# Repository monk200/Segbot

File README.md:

# Segbot

This repository contains files such as code, CAD files, Matlab simulations, and brainstorming documents from my work designing and developing a two-wheeled balancing robot. The project can be split into two main parts: designing the system and developing the real-world version of the system. The original design was done in my [Mechatronics](http://coecsl.ece.illinois.edu/ge423/) course as a final project for Spring 2020 but the real robot was built and programmed in the course [Computer Control of Mechanical Systems](http://coecsl.ece.illinois.edu/me461/) in Fall 2020. Both courses were led by UIUC Prof. Dan Block, the university's Control Systems Lab Manager. Prof. Block created a guide to building a Segbot at [this link](http://coecsl.ece.illinois.edu/segbot/segbot.html) and his guidance and expertise was absolutely essential in all steps of this project.  

## Designing the System
Because of the COVID-19 pandemic, Prof. Block restructured the final project of Mechatronics to be to design a Segbot from scratch. At the time, the [Mechatronics course used the MPS430G2553 microcontroller](https://github.com/monk200/Mechatronics_with_MSP430G2553) so all of the initial design choices and considerations were made keeping that in mind. I compiled a list of parts that were essential for desiging a PCB that would interface with the microcontroller. I was also tasked with creating a CAD model of the robot body and using its parameters, as well as the parameters of the motors, to tune a simulation to balance the Segbot. The last portion of the designing process was to create pseudocode for how the robot needed to behave to balance, solving the inverted pendulum problem. Below you can find a list of each step in the process:  
* [Creating a parts list](https://github.com/monk200/Segbot/blob/main/Parts_Lists/Initial_Parts_List.md): This document includes a list of each part, a link to an online retailor to buy the part, and a link to its datasheet. Most parts also include commentary on the thought process behind choosing the specified part.  
* [Initial wiring configuration](https://github.com/monk200/Segbot/blob/main/Wiring/Initial%20Design%20Wiring%20Diagram.png): This image was created and iterated upon when planning out how the system needs to be connected electronically. This was done as an intermediate step before desiging the PCB in EagleCAD because the color-coding made it quick and easy to troubleshoot and discuss.  
* [PCB design](https://github.com/monk200/Segbot/tree/main/Wiring/Initial%20EagleCAD%20Files): EagleCAD was used to design a PCB that the MSP430 would sit onto. Some parts needed to be created from scratch but otherwise it is a very minimal board.  
* [CAD model](https://github.com/monk200/Segbot/tree/main/Frame/Initial%20Frame%20Design): Autodesk Fusion 360 was used to design a body for the Segbot that would ideally be 3D-printed in UIUC's ISE design lab.  
* [Matlab model](https://github.com/monk200/Segbot/tree/main/Matlab_Simulation/Initial%20Simulation%20Files): A simulation animation and framework were provided by Prof. Block. The parameters from the previous stages of the design process were input into the model and it was manually tuned to balance. This step is useful as a proof-of-concept and as an excersie for students to get experience tuning a control system.  

## Developing the System
While Prof. Block signed off on the original design as feasible, since the second part of this project was done as part of a different course it didn't use the exact same design. Prof. Block upgraded to using the [TMS320F28379D microcontroller](https://github.com/monk200/Mechatronics_with_TMS320F28379D), added a variety of peripherals to the PCB, and simplified the body of the Segbot. For the sake of being thorough, the points below include information on each stage of the design process and how they've changed:  
* [Parts list](https://github.com/monk200/Segbot/blob/main/Parts_Lists/Revised_Parts_List.md): This document lists the essential parts used in the new Segbot design and how they compare to the specs of the previously chosen parts.  
* [Wiring configuration](https://github.com/monk200/Segbot/blob/main/Wiring/Reworked%20Wiring%20Diagram.png): This image is again a color-coded wiring schematic to show a quick layout of how the new components are connected.  
* [PCB design](https://github.com/monk200/Segbot/tree/main/Wiring/Reworked%20EagleCAD%20Files): This folder contains the new EagleCAD files for the PCB. As stated earlier, this is a much more complicated design because a lot of peripherals were added to allow the board to be used for exploring other applications.  
* [CAD model](https://github.com/monk200/Segbot/tree/main/Frame/Reworked%20Frame%20Design): A much simpler design, this design is only two 3D-printed legs to be attached to the PCB itself.  

With a new physical design, the Matlab model needed to be redone but this time since the physical parts were present the tuning was much more reliable. Throughout the [Computer Control of Mechanical Systems](https://github.com/monk200/Mechatronics_with_TMS320F28379D) course, the new microcontroller was explolred and experimented with. Near the end of the semester, I programmed the board to implement control algorithms to solve the inverted pendulum problem and control the robot's motion. The links below lead to details on each step of this process:  
* [Matlab model](https://github.com/monk200/Segbot/tree/main/Matlab_Simulation/Reworked%20SImulation%20Files): Using the same simulation as before but new, more accurate, parameters, I manually tuned the Segbot to balance.  
* [Programming](https://github.com/monk200/Segbot/tree/main/Code): This link goes to the code for the project with extensive details on the processes used and how to set it up on the hardware.  

## Final Product
Below are links to several videos demonstrating different portions of the Segbot's performance:  

### Controlling the Segbot with the Keyboard
  
[Github Video Link](https://github.com/monk200/Segbot/blob/main/Working%20Demo%20Video.mp4)  

### Balancing Segbot

### The Stable Simulation

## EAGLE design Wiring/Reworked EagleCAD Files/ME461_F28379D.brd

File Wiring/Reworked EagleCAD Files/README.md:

# PCB for Reworked Design
Prof. Block used EagleCAD to design the circuit board for the reworked design. The circuit schematic can be seen to connect each part in the way my [reworked wiring diagram](https://github.com/monk200/Segbot/blob/main/Wiring/Initial%20Design%20Wiring%20Diagram.png) does, but my diagram only has the essential peripherials to make the Segbot work. The board was fabricated at https://www.4pcb.com/ and my professor uses its [free file checker](https://www.4pcb.com/free-pcb-file-check/index.html).  

## Wiring Considerations
This board design is significantly more complex because the board was designed with the intent of using it for any number of personal projects. My initial design minimized complexity because I was focusing on the project at hand and I am less experienced than my Professor. When looking through his design, he added a switch to power the motor subassembly on and off and a potentiometer for each motor connected to the H-bridge's VREF pin. This allows the user to regulate the maximum motor current. Other major changes from my design include that Prof. Block's design needs to have an external real-time clock but does not need external quadrature encoders. The most complex difference between my design and Prof. Block's design is the power system. Prof. Block designed this PCB to be able to be powered by an AC outlet or by a DC battery pack. Since the Segbot is a mobile project, I only focused on deconstructing the DC power system.  

## EagleCAD Design

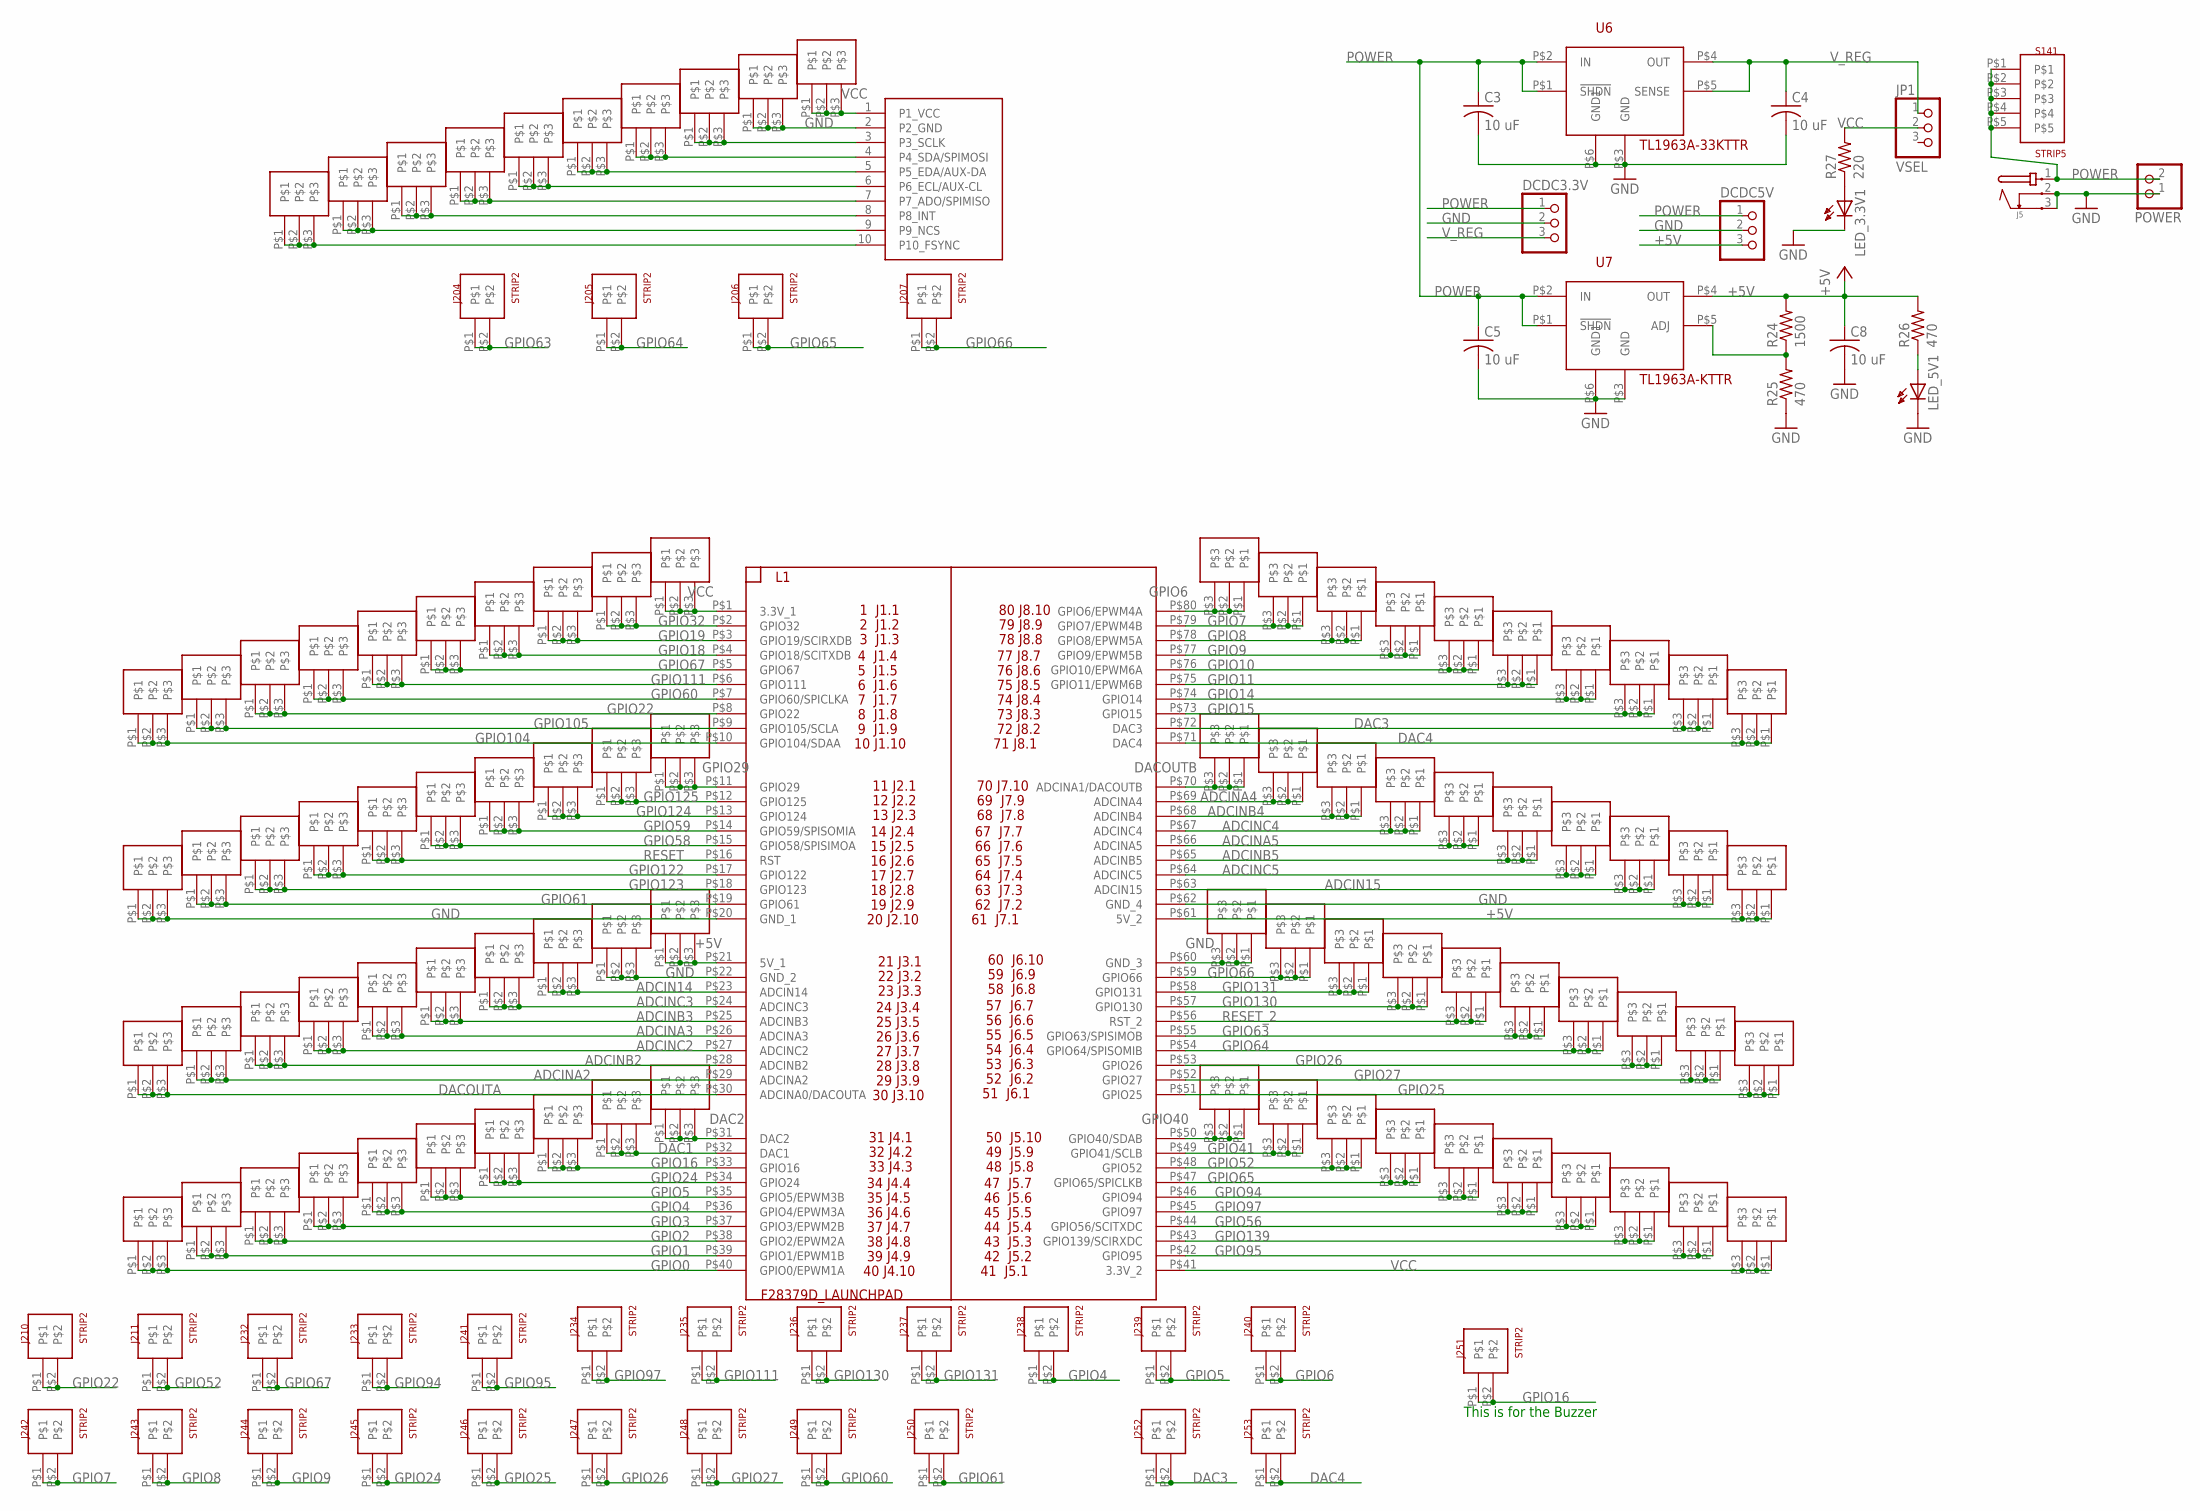
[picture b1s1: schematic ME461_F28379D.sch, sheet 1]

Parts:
C3, C4, C5, C8: 10 uF; C1206
DCDC3.3V, DCDC5V: PINHD-1X3; 1X03
J5: JACK-PMS
J10, J14, J15, J16, J17, J18, J19, J20, J21, J28, J29, J30, J31, J32, J33, J98, J99, J100, J101, J102, J103, J104, J105, J106, J107, J108, J109, J110, J111, J112, J113, J114, J115, J116, J117, J118, J119, J120, J121, J122, J123, J124, J125, J126, J127, J128, J129, J130, J131, J132, J133, J134, J135, J136, J137, J138, J139, J140, J141, J142, J143, J144, J145, J146, J147, J148, J149, J150, J151, J152, J153, J154, J155, J156, J157, J158, J159, J160, J161, J162, J163, J164, J165, J166, J167, J168, J169, J170, J176, J177: STRIP3
J204, J205, J206, J207, J210, J211, J232, J233, J234, J235, J236, J237, J238, J239, J240, J241, J242, J243, J244, J245, J246, J247, J248, J249, J250, J251, J252, J253: STRIP2
JP1: VSEL; 1X03
L1: F28379D_LAUNCHPAD
LED_3.3V1, LED_5V1: LED3MM
POWER: PINHD-1X2; 1X02
R24: 1500; M1206
R25, R26: 470; M1206
R27: 220; M1206
S141: STRIP5
U6: TL1963A-33KTTR; TL1963AKTTR
U7: TL1963A-KTTR; TL1963AKTTR
U$1: MPU-9250-BB

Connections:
+5V: C8.1, DCDC5V.3, J103.P$1, J103.P$2, J103.P$3, J152.P$1, J152.P$2, J152.P$3, L1.P$21 (5V_1), L1.P$61 (5V_2), R24.2, R26.2, U7.P$4 (OUT); also elsewhere on the board
ADCIN14: J105.P$1, J105.P$2, J105.P$3, L1.P$23 (ADCIN14)
ADCIN15: J150.P$1, J150.P$2, J150.P$3, L1.P$63 (ADCIN15)
ADCINA2: J111.P$1, J111.P$2, J111.P$3, L1.P$29 (ADCINA2)
ADCINA3: J108.P$1, J108.P$2, J108.P$3, L1.P$26 (ADCINA3)
ADCINA4: J144.P$1, J144.P$2, J144.P$3, L1.P$69 (ADCINA4)
ADCINA5: J147.P$1, J147.P$2, J147.P$3, L1.P$66 (ADCINA5)
ADCINB2: J110.P$1, J110.P$2, J110.P$3, L1.P$28 (ADCINB2)
ADCINB3: J107.P$1, J107.P$2, J107.P$3, L1.P$25 (ADCINB3)
ADCINB4: J145.P$1, J145.P$2, J145.P$3, L1.P$68 (ADCINB4)
ADCINB5: J148.P$1, J148.P$2, J148.P$3, L1.P$65 (ADCINB5)
ADCINC2: J109.P$1, J109.P$2, J109.P$3, L1.P$27 (ADCINC2)
ADCINC3: J106.P$1, J106.P$2, J106.P$3, L1.P$24 (ADCINC3)
ADCINC4: J146.P$1, J146.P$2, J146.P$3, L1.P$67 (ADCINC4)
ADCINC5: J149.P$1, J149.P$2, J149.P$3, L1.P$64 (ADCINC5)
DAC1: J114.P$1, J114.P$2, J114.P$3, L1.P$32 (DAC1)
DAC2: J113.P$1, J113.P$2, J113.P$3, L1.P$31 (DAC2)
DAC3: J141.P$1, J141.P$2, J141.P$3, J252.P$1, J252.P$2, L1.P$72 (DAC3)
DAC4: J142.P$1, J142.P$2, J142.P$3, J253.P$1, J253.P$2, L1.P$71 (DAC4)
DACOUTA: J112.P$1, J112.P$2, J112.P$3, L1.P$30 (ADCINA0/DACOUTA)
DACOUTB: J143.P$1, J143.P$2, J143.P$3, L1.P$70 (ADCINA1/DACOUTB)
GND: C3.2, C4.2, C5.2, C8.2, DCDC3.3V.2, DCDC5V.2, J5.2, J5.3, J102.P$1, J102.P$2, J102.P$3, J104.P$1, J104.P$2, J104.P$3, J124.P$1, J124.P$2, J124.P$3, J151.P$1, J151.P$2, J151.P$3, J153.P$1, J153.P$2, J153.P$3, L1.P$20 (GND_1), L1.P$22 (GND_2), L1.P$60 (GND_3), L1.P$62 (GND_4), LED_3.3V1.K (C), LED_5V1.K (C), POWER.1, R25.1, U6.P$3 (GND), U6.P$6 (GND1), U7.P$3 (GND), U7.P$6 (GND1), U$1.2 (P2_GND); also elsewhere on the board
GPIO0: J122.P$1, J122.P$2, J122.P$3, L1.P$40 (GPIO0/EPWM1A)
GPIO1: J121.P$1, J121.P$2, J121.P$3, L1.P$39 (GPIO1/EPWM1B)
GPIO2: J120.P$1, J120.P$2, J120.P$3, L1.P$38 (GPIO2/EPWM2A); also elsewhere on the board
GPIO3: J119.P$1, J119.P$2, J119.P$3, L1.P$37 (GPIO3/EPWM2B); also elsewhere on the board
GPIO4: J118.P$1, J118.P$2, J118.P$3, J238.P$1, J238.P$2, L1.P$36 (GPIO4/EPWM3A)
GPIO5: J117.P$1, J117.P$2, J117.P$3, J239.P$1, J239.P$2, L1.P$35 (GPIO5/EPWM3B)
GPIO6: J133.P$1, J133.P$2, J133.P$3, J240.P$1, J240.P$2, L1.P$80 (GPIO6/EPWM4A)
GPIO7: J134.P$1, J134.P$2, J134.P$3, J242.P$1, J242.P$2, L1.P$79 (GPIO7/EPWM4B)
GPIO8: J135.P$1, J135.P$2, J135.P$3, J243.P$1, J243.P$2, L1.P$78 (GPIO8/EPWM5A)
GPIO9: J136.P$1, J136.P$2, J136.P$3, J244.P$1, J244.P$2, L1.P$77 (GPIO9/EPWM5B)
GPIO10: J137.P$1, J137.P$2, J137.P$3, L1.P$76 (GPIO10/EPWM6A); also elsewhere on the board
GPIO11: J138.P$1, J138.P$2, J138.P$3, L1.P$75 (GPIO11/EPWM6B); also elsewhere on the board
GPIO14: J139.P$1, J139.P$2, J139.P$3, L1.P$74 (GPIO14); also elsewhere on the board
GPIO15: J140.P$1, J140.P$2, J140.P$3, L1.P$73 (GPIO15); also elsewhere on the board
GPIO16: J115.P$1, J115.P$2, J115.P$3, J251.P$1, J251.P$2, L1.P$33 (GPIO16)
GPIO18: J16.P$1, J16.P$2, J16.P$3, L1.P$4 (GPIO18/SCITXDB)
GPIO19: J15.P$1, J15.P$2, J15.P$3, L1.P$3 (GPIO19/SCIRXDB)
GPIO22: J20.P$1, J20.P$2, J20.P$3, J210.P$1, J210.P$2, L1.P$8 (GPIO22)
GPIO24: J116.P$1, J116.P$2, J116.P$3, J245.P$1, J245.P$2, L1.P$34 (GPIO24)
GPIO25: J162.P$1, J162.P$2, J162.P$3, J246.P$1, J246.P$2, L1.P$51 (GPIO25)
GPIO26: J160.P$1, J160.P$2, J160.P$3, J247.P$1, J247.P$2, L1.P$53 (GPIO26)
GPIO27: J161.P$1, J161.P$2, J161.P$3, J248.P$1, J248.P$2, L1.P$52 (GPIO27)
GPIO29: J29.P$1, J29.P$2, J29.P$3, L1.P$11 (GPIO29); also elsewhere on the board
GPIO32: J14.P$1, J14.P$2, J14.P$3, L1.P$2 (GPIO32); also elsewhere on the board
GPIO40: J163.P$1, J163.P$2, J163.P$3, L1.P$50 (GPIO40/SDAB); also elsewhere on the board
GPIO41: J164.P$1, J164.P$2, J164.P$3, L1.P$49 (GPIO41/SCLB); also elsewhere on the board
GPIO52: J165.P$1, J165.P$2, J165.P$3, J211.P$1, J211.P$2, L1.P$48 (GPIO52)
GPIO56: J169.P$1, J169.P$2, J169.P$3, L1.P$44 (GPIO56/SCITXDC)
GPIO58: J33.P$1, J33.P$2, J33.P$3, L1.P$15 (GPIO58/SPISIMOA)
GPIO59: J32.P$1, J32.P$2, J32.P$3, L1.P$14 (GPIO59/SPISOMIA)
GPIO60: J19.P$1, J19.P$2, J19.P$3, J249.P$1, J249.P$2, L1.P$7 (GPIO60/SPICLKA)
GPIO61: J101.P$1, J101.P$2, J101.P$3, J250.P$1, J250.P$2, L1.P$19 (GPIO61)
GPIO63: J158.P$1, J158.P$2, J158.P$3, J204.P$1, J204.P$2, L1.P$55 (GPIO63/SPISIMOB)
GPIO64: J159.P$1, J159.P$2, J159.P$3, J205.P$1, J205.P$2, L1.P$54 (GPIO64/SPISOMIB)
GPIO65: J166.P$1, J166.P$2, J166.P$3, J206.P$1, J206.P$2, L1.P$47 (GPIO65/SPICLKB)
GPIO66: J154.P$1, J154.P$2, J154.P$3, J207.P$1, J207.P$2, L1.P$59 (GPIO66)
GPIO67: J17.P$1, J17.P$2, J17.P$3, J232.P$1, J232.P$2, L1.P$5 (GPIO67)
GPIO94: J167.P$1, J167.P$2, J167.P$3, J233.P$1, J233.P$2, L1.P$46 (GPIO94)
GPIO95: J176.P$1, J176.P$2, J176.P$3, J241.P$1, J241.P$2, L1.P$42 (GPIO95)
GPIO97: J168.P$1, J168.P$2, J168.P$3, J234.P$1, J234.P$2, L1.P$45 (GPIO97)
GPIO104: J28.P$1, J28.P$2, J28.P$3, L1.P$10 (GPIO104/SDAA)
GPIO105: J21.P$1, J21.P$2, J21.P$3, L1.P$9 (GPIO105/SCLA)
GPIO111: J18.P$1, J18.P$2, J18.P$3, J235.P$1, J235.P$2, L1.P$6 (GPIO111)
GPIO122: J99.P$1, J99.P$2, J99.P$3, L1.P$17 (GPIO122); also elsewhere on the board
GPIO123: J100.P$1, J100.P$2, J100.P$3, L1.P$18 (GPIO123); also elsewhere on the board
GPIO124: J31.P$1, J31.P$2, J31.P$3, L1.P$13 (GPIO124); also elsewhere on the board
GPIO125: J30.P$1, J30.P$2, J30.P$3, L1.P$12 (GPIO125); also elsewhere on the board
GPIO130: J156.P$1, J156.P$2, J156.P$3, J236.P$1, J236.P$2, L1.P$57 (GPIO130)
GPIO131: J155.P$1, J155.P$2, J155.P$3, J237.P$1, J237.P$2, L1.P$58 (GPIO131)
GPIO139: J170.P$1, J170.P$2, J170.P$3, L1.P$43 (GPIO139/SCIRXDC)
unnamed: R24.1, R25.2, U7.P$5 (ADJ)
unnamed: LED_5V1.A, R26.1
unnamed: LED_3.3V1.A, R27.1
unnamed: J125.P$1, J125.P$2, J125.P$3, U$1.3 (P3_SCLK)
unnamed: J126.P$1, J126.P$2, J126.P$3, U$1.4 (P4_SDA/SPIMOSI)
unnamed: J127.P$1, J127.P$2, J127.P$3, U$1.5 (P5_EDA/AUX-DA)
unnamed: J128.P$1, J128.P$2, J128.P$3, U$1.6 (P6_ECL/AUX-CL)
unnamed: J129.P$1, J129.P$2, J129.P$3, U$1.7 (P7_ADO/SPIMISO)
unnamed: J130.P$1, J130.P$2, J130.P$3, U$1.8 (P8_INT)
unnamed: J131.P$1, J131.P$2, J131.P$3, U$1.9 (P9_NCS)
unnamed: J132.P$1, J132.P$2, J132.P$3, U$1.10 (P10_FSYNC)
POWER: C3.1, C5.1, DCDC3.3V.1, DCDC5V.1, J5.1, POWER.2, S141.P$1, S141.P$2, S141.P$3, S141.P$4, S141.P$5, U6.P$1 (!SHDN), U6.P$2 (IN), U7.P$1 (!SHDN), U7.P$2 (IN); also elsewhere on the board
RESET: J98.P$1, J98.P$2, J98.P$3, L1.P$16 (RST)
RESET_2: J157.P$1, J157.P$2, J157.P$3, L1.P$56 (RST_2)
VCC: J10.P$1, J10.P$2, J10.P$3, J123.P$1, J123.P$2, J123.P$3, J177.P$1, J177.P$2, J177.P$3, JP1.2, L1.P$1 (3.3V_1), L1.P$41 (3.3V_2), R27.2, U$1.1 (P1_VCC); also elsewhere on the board
V_REG: C4.1, DCDC3.3V.3, JP1.1, U6.P$4 (OUT), U6.P$5 (SENSE)

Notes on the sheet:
This is for the Buzzer

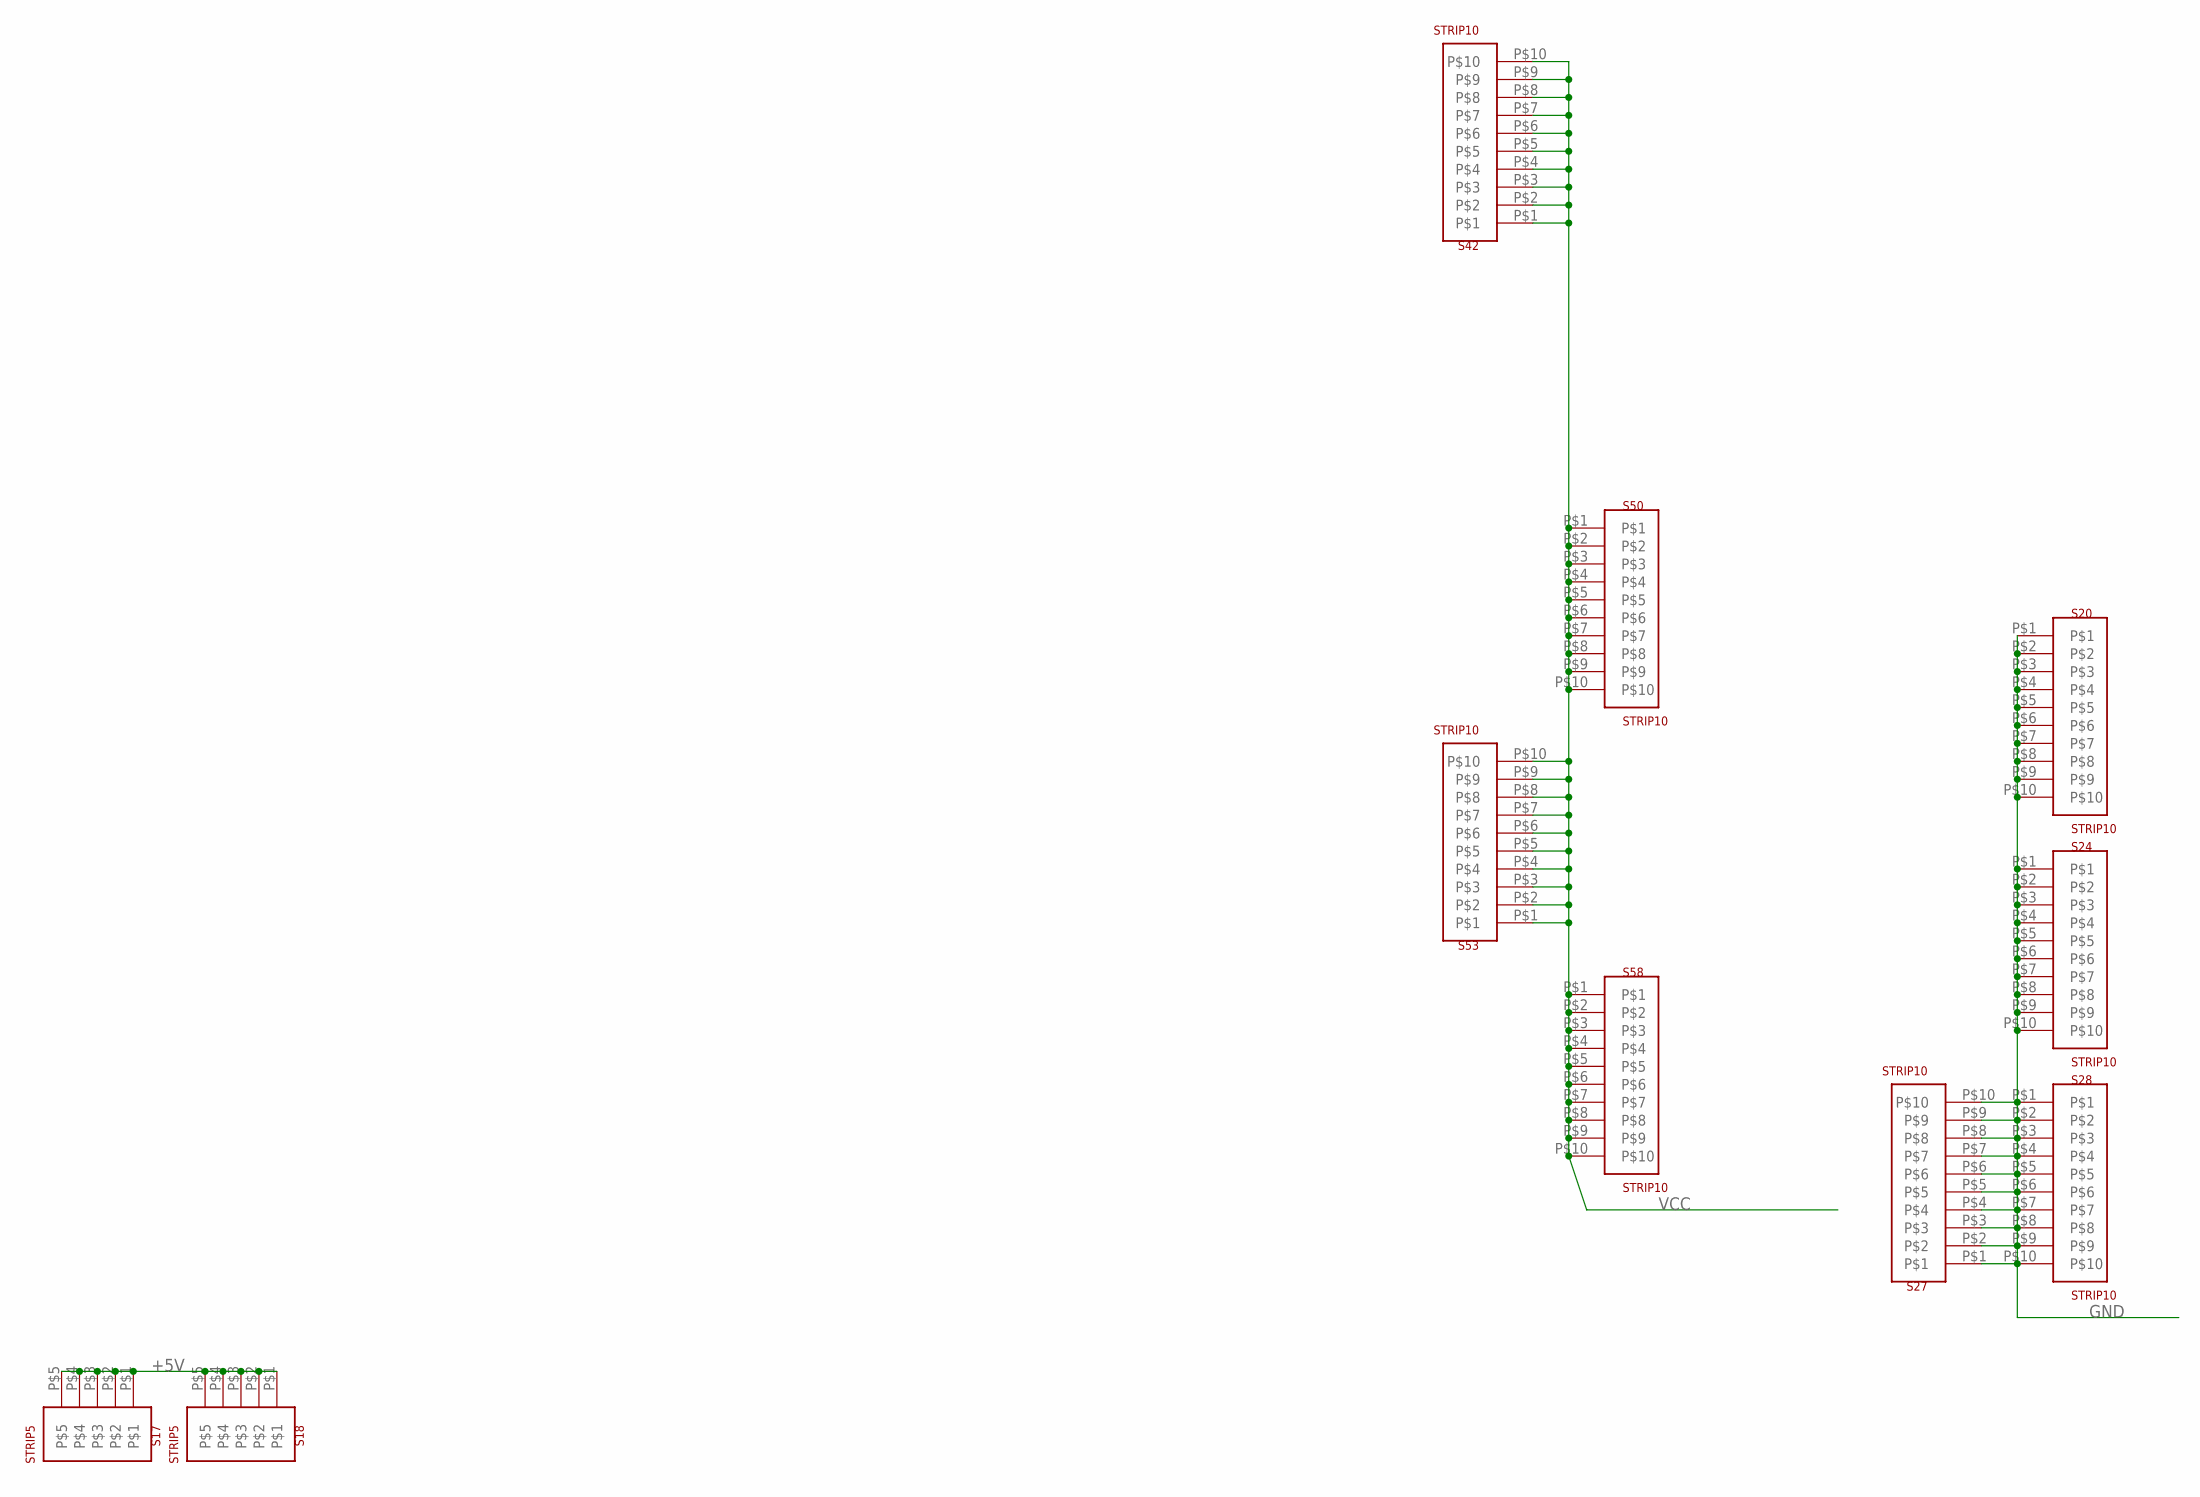
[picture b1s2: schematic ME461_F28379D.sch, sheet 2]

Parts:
S17, S18: STRIP5
S20, S24, S27, S28, S42, S50, S53, S58: STRIP10

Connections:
+5V: S17.P$1, S17.P$2, S17.P$3, S17.P$4, S17.P$5, S18.P$1, S18.P$2, S18.P$3, S18.P$4, S18.P$5; also elsewhere on the board
GND: S20.P$1, S20.P$2, S20.P$3, S20.P$4, S20.P$5, S20.P$6, S20.P$7, S20.P$8, S20.P$9, S20.P$10, S24.P$1, S24.P$2, S24.P$3, S24.P$4, S24.P$5, S24.P$6, S24.P$7, S24.P$8, S24.P$9, S24.P$10, S27.P$1, S27.P$2, S27.P$3, S27.P$4, S27.P$5, S27.P$6, S27.P$7, S27.P$8, S27.P$9, S27.P$10, S28.P$1, S28.P$2, S28.P$3, S28.P$4, S28.P$5, S28.P$6, S28.P$7, S28.P$8, S28.P$9, S28.P$10; also elsewhere on the board
VCC: S42.P$1, S42.P$2, S42.P$3, S42.P$4, S42.P$5, S42.P$6, S42.P$7, S42.P$8, S42.P$9, S42.P$10, S50.P$1, S50.P$2, S50.P$3, S50.P$4, S50.P$5, S50.P$6, S50.P$7, S50.P$8, S50.P$9, S50.P$10, S53.P$1, S53.P$2, S53.P$3, S53.P$4, S53.P$5, S53.P$6, S53.P$7, S53.P$8, S53.P$9, S53.P$10, S58.P$1, S58.P$2, S58.P$3, S58.P$4, S58.P$5, S58.P$6, S58.P$7, S58.P$8, S58.P$9, S58.P$10; also elsewhere on the board

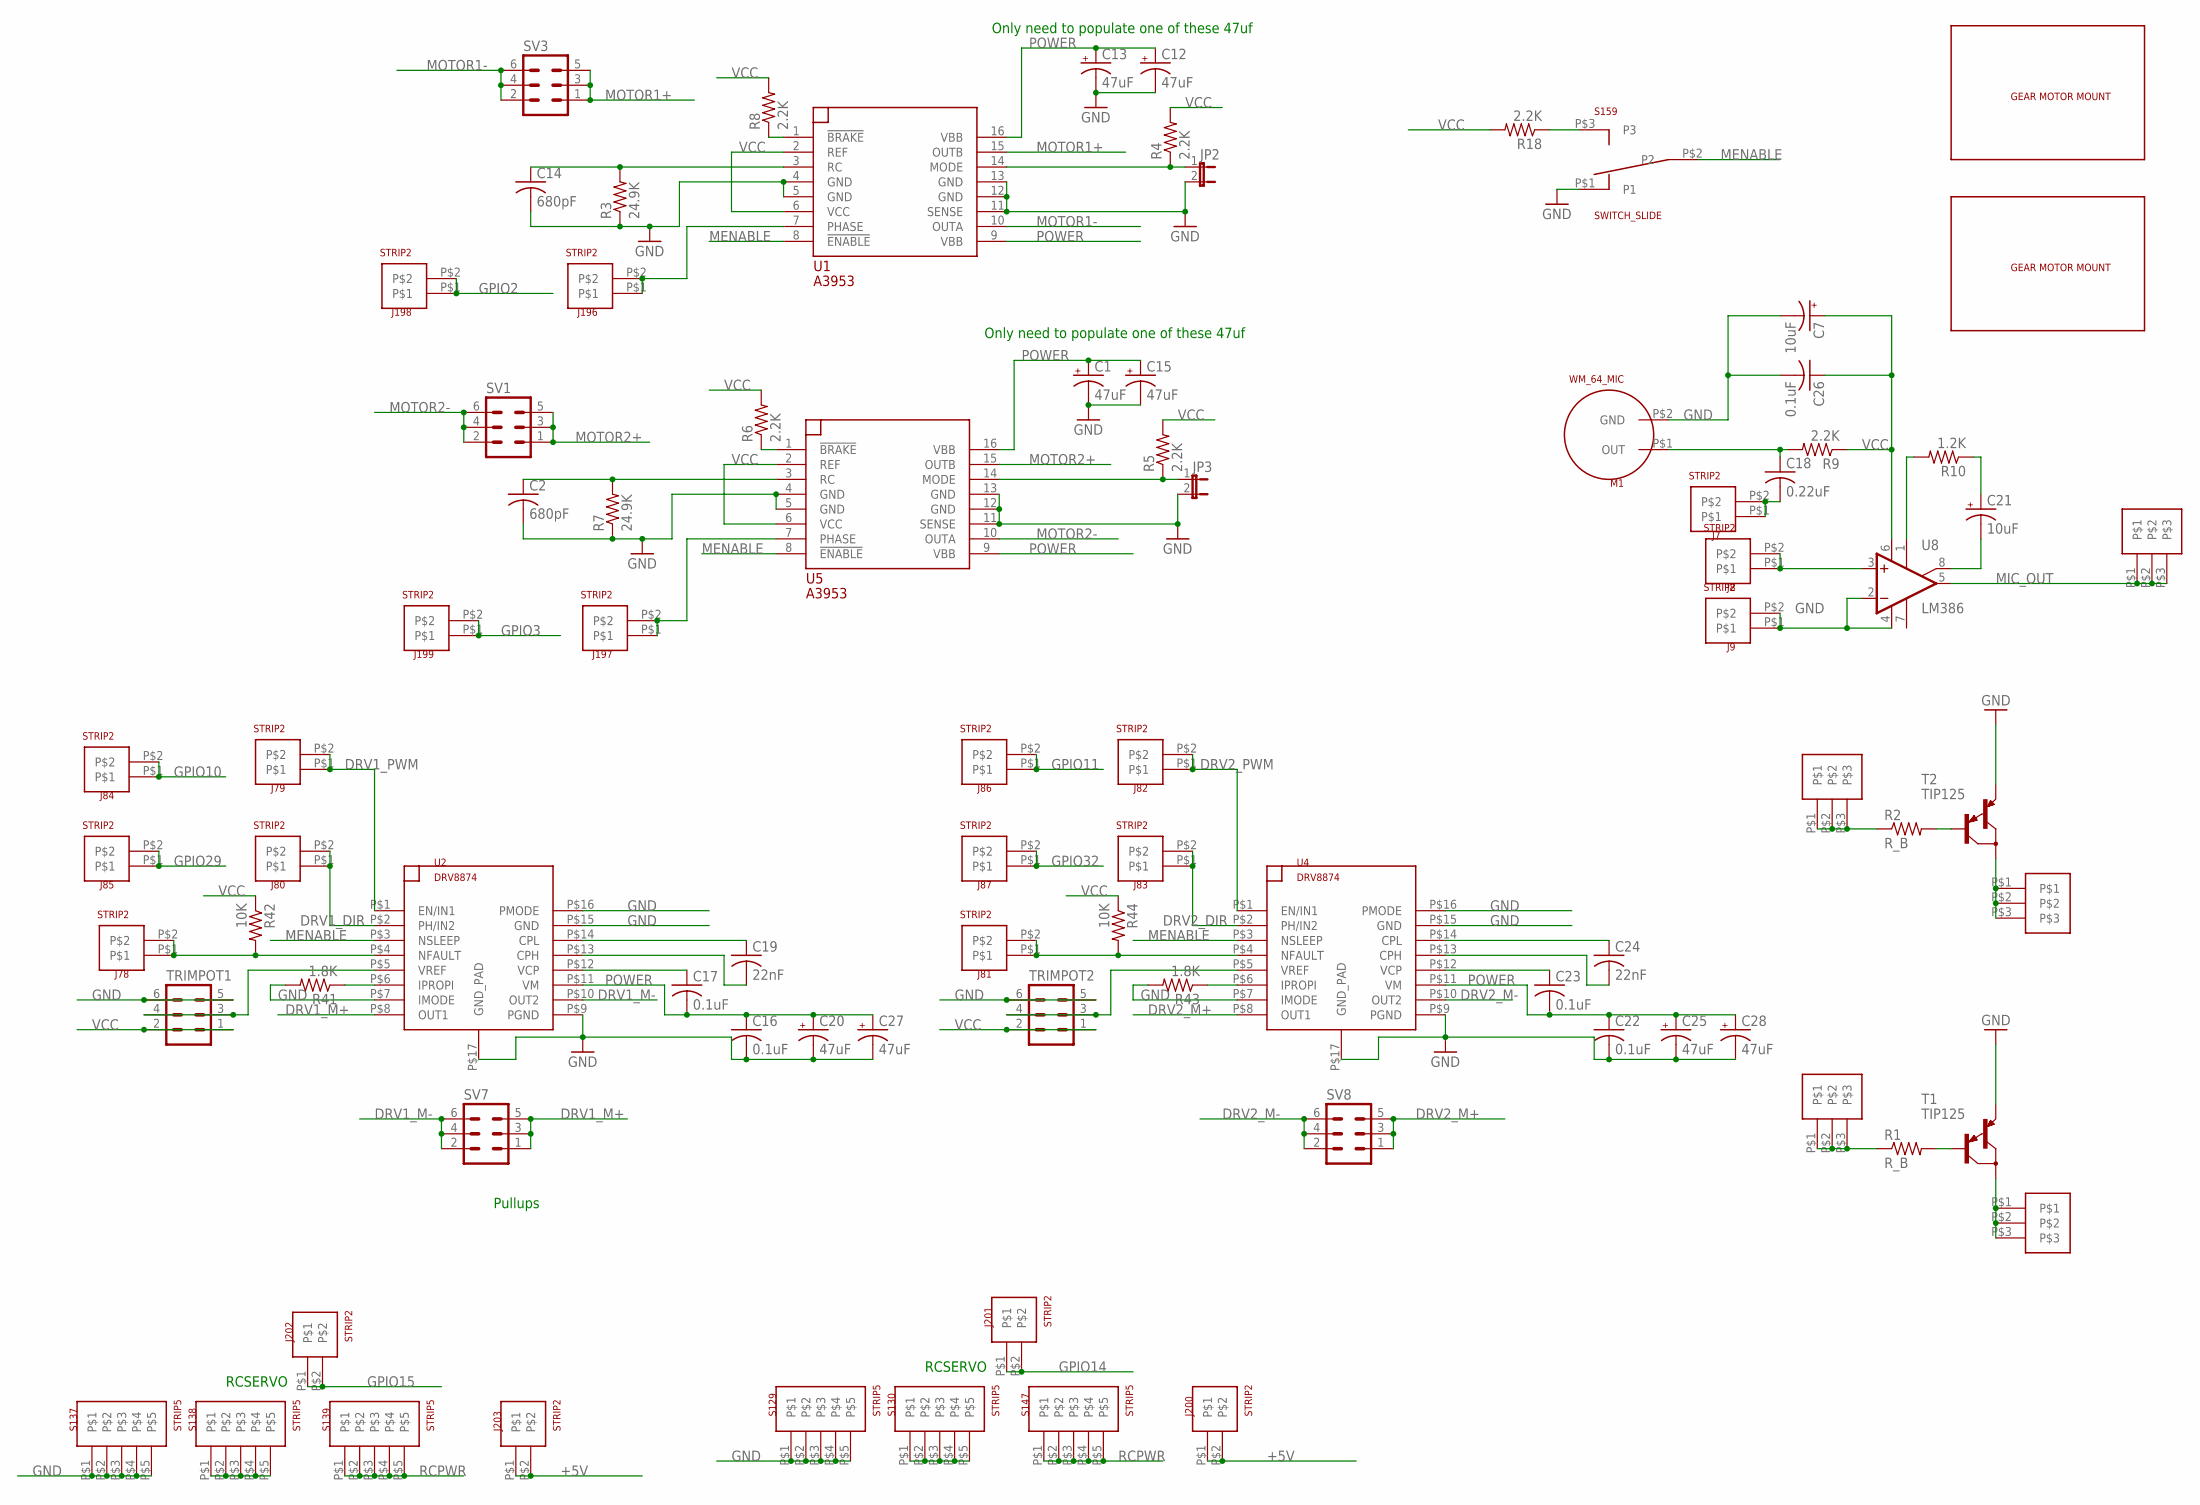
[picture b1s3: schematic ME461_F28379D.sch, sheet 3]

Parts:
C1, C12, C13, C15, C20, C25, C27, C28: 47uF; 153CLV-0810
C2, C14: 680pF; C1206
C7, C21: 10uF; E2,5-6
C16, C17, C22, C23: 0.1uF; C1206
C18: 0.22uF; C050-025X075
C19, C24: 22nF; C1206
C26: 0.1uF; C050-025X075
J4, J6, J23, J24, J49: STRIP3
J7, J8, J9, J78, J79, J80, J81, J82, J83, J84, J85, J86, J87, J196, J197, J198, J199, J200, J201, J202, J203: STRIP2
JP2, JP3: JP1E; JP1
M1: WM_64_MIC
R1, R2: R_B; 0207/10
R3, R7: 24.9K; M1206
R4, R5, R6, R8, R18: 2.2K; M1206
R9: 2.2K; 0207/10
R10: 1.2K; 0207/10
R41, R43: 1.8K; M1206
R42, R44: 10K; M1206
S129, S130, S137, S138, S139, S147: STRIP5
S159: SWITCH_SLIDE
SV1, SV3, SV7, SV8: MA03-2
T1, T2: TIP125; TO220
TRIMPOT1, TRIMPOT2: MA03-2
U1, U5: A3953; SO16W
U2, U4: DRV8874; HTSSOP16
U8: LM386; DIL08
U$2, U$3: GEARMOTOR_MOUNT

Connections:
+5V: J200.P$1, J200.P$2, J203.P$1, J203.P$2; also elsewhere on the board
DRV1_DIR: J80.P$1, J80.P$2, U2.P$2 (PH/IN2)
DRV1_M+: SV7.1, SV7.3, SV7.5, U2.P$8 (OUT1)
DRV1_M-: SV7.2, SV7.4, SV7.6, U2.P$10 (OUT2)
DRV1_PWM: J79.P$1, J79.P$2, U2.P$1 (EN/IN1)
DRV2_DIR: J83.P$1, J83.P$2, U4.P$2 (PH/IN2)
DRV2_M+: SV8.1, SV8.3, SV8.5, U4.P$8 (OUT1)
DRV2_M-: SV8.2, SV8.4, SV8.6, U4.P$10 (OUT2)
DRV2_PWM: J82.P$1, J82.P$2, U4.P$1 (EN/IN1)
GND: C1.-, C2.2, C7.-, C12.-, C13.-, C14.2, C15.-, C16.2, C20.-, C22.2, C25.-, C26.2, C27.-, C28.-, J9.P$1, J9.P$2, JP2.2, JP3.2, M1.P$2 (GND), R3.1, R7.1, R41.2, R43.2, S129.P$1, S129.P$2, S129.P$3, S129.P$4, S129.P$5, S137.P$1, S137.P$2, S137.P$3, S137.P$4, S137.P$5, S159.P$1 (P1), T1.3 (E), T2.3 (E), TRIMPOT1.5, TRIMPOT1.6, TRIMPOT2.5, TRIMPOT2.6, U1.4 (GND), U1.5 (GND), U1.11 (SENSE), U1.12 (GND), U1.13 (GND), U2.P$7 (IMODE), U2.P$9 (PGND), U2.P$15 (GND), U2.P$16 (PMODE), U2.P$17 (GND_PAD), U4.P$7 (IMODE), U4.P$9 (PGND), U4.P$15 (GND), U4.P$16 (PMODE), U4.P$17 (GND_PAD), U5.4 (GND), U5.5 (GND), U5.11 (SENSE), U5.12 (GND), U5.13 (GND), U8.2 (-IN), U8.4 (GND); also elsewhere on the board
GPIO2: J198.P$1, J198.P$2; also elsewhere on the board
GPIO3: J199.P$1, J199.P$2; also elsewhere on the board
GPIO10: J84.P$1, J84.P$2; also elsewhere on the board
GPIO11: J86.P$1, J86.P$2; also elsewhere on the board
GPIO14: J201.P$1, J201.P$2; also elsewhere on the board
GPIO15: J202.P$1, J202.P$2; also elsewhere on the board
GPIO29: J85.P$1, J85.P$2; also elsewhere on the board
GPIO32: J87.P$1, J87.P$2; also elsewhere on the board
MENABLE: S159.P$2 (P2), U1.8 (!ENABLE), U2.P$3 (NSLEEP), U4.P$3 (NSLEEP), U5.8 (!ENABLE)
MIC_OUT: J49.P$1, J49.P$2, J49.P$3, U8.5 (OUT)
MOTOR1+: SV3.1, SV3.3, SV3.5, U1.15 (OUTB)
MOTOR1-: SV3.2, SV3.4, SV3.6, U1.10 (OUTA)
MOTOR2+: SV1.1, SV1.3, SV1.5, U5.15 (OUTB)
MOTOR2-: SV1.2, SV1.4, SV1.6, U5.10 (OUTA)
unnamed: R2.2, T2.1 (B)
unnamed: R1.2, T1.1 (B)
unnamed: S138.P$1, S138.P$2, S138.P$3, S138.P$4, S138.P$5
unnamed: C21.-, U8.8 (GAIN2)
unnamed: R10.2, U8.1 (GAIN1)
unnamed: C21.+, R10.1
unnamed: C18.2, J7.P$1, J7.P$2
unnamed: C18.1, M1.P$1 (OUT), R9.2
unnamed: R6.1, U5.1 (!BRAKE)
unnamed: C2.1, R7.2, U5.3 (RC)
unnamed: R8.1, U1.1 (!BRAKE)
unnamed: C14.1, R3.2, U1.3 (RC)
unnamed: JP2.1, R4.1, U1.14 (MODE)
unnamed: R18.1, S159.P$3 (P3)
unnamed: JP3.1, R5.1, U5.14 (MODE)
unnamed: C19.1, U2.P$14 (CPL)
unnamed: C19.2, U2.P$13 (CPH)
unnamed: C17.1, U2.P$12 (VCP)
unnamed: R43.1, U4.P$6 (IPROPI)
unnamed: R41.1, U2.P$6 (IPROPI)
unnamed: J78.P$1, J78.P$2, R42.2, U2.P$4 (NFAULT)
unnamed: TRIMPOT1.3, TRIMPOT1.4, U2.P$5 (VREF)
unnamed: C24.1, U4.P$14 (CPL)
unnamed: C24.2, U4.P$13 (CPH)
unnamed: C23.1, U4.P$12 (VCP)
unnamed: J81.P$1, J81.P$2, R44.2, U4.P$4 (NFAULT)
unnamed: TRIMPOT2.3, TRIMPOT2.4, U4.P$5 (VREF)
unnamed: S130.P$1, S130.P$2, S130.P$3, S130.P$4, S130.P$5
unnamed: J8.P$1, J8.P$2, U8.3 (+IN)
unnamed: J196.P$1, J196.P$2, U1.7 (PHASE)
unnamed: J197.P$1, J197.P$2, U5.7 (PHASE)
POWER: C1.+, C12.+, C13.+, C15.+, C16.1, C17.2, C20.+, C22.1, C23.2, C25.+, C27.+, C28.+, U1.9 (VBB), U1.16 (VBB), U2.P$11 (VM), U4.P$11 (VM), U5.9 (VBB), U5.16 (VBB); also elsewhere on the board
RCPWR: S139.P$1, S139.P$2, S139.P$3, S139.P$4, S139.P$5, S147.P$1, S147.P$2, S147.P$3, S147.P$4, S147.P$5
TR_BASE: J6.P$1, J6.P$2, J6.P$3, R1.1
TR_BASE1: J24.P$1, J24.P$2, J24.P$3, R2.1
TR_LOAD: J4.P$1, J4.P$2, J4.P$3, T1.2 (C)
TR_LOAD1: J23.P$1, J23.P$2, J23.P$3, T2.2 (C)
VCC: C7.+, C26.1, R4.2, R5.2, R6.2, R8.2, R9.1, R18.2, R42.1, R44.1, TRIMPOT1.1, TRIMPOT1.2, TRIMPOT2.1, TRIMPOT2.2, U1.2 (REF), U1.6 (VCC), U5.2 (REF), U5.6 (VCC), U8.6 (VS); also elsewhere on the board

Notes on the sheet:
Pullups
RCSERVO
Only need to populate one of these 47uf
